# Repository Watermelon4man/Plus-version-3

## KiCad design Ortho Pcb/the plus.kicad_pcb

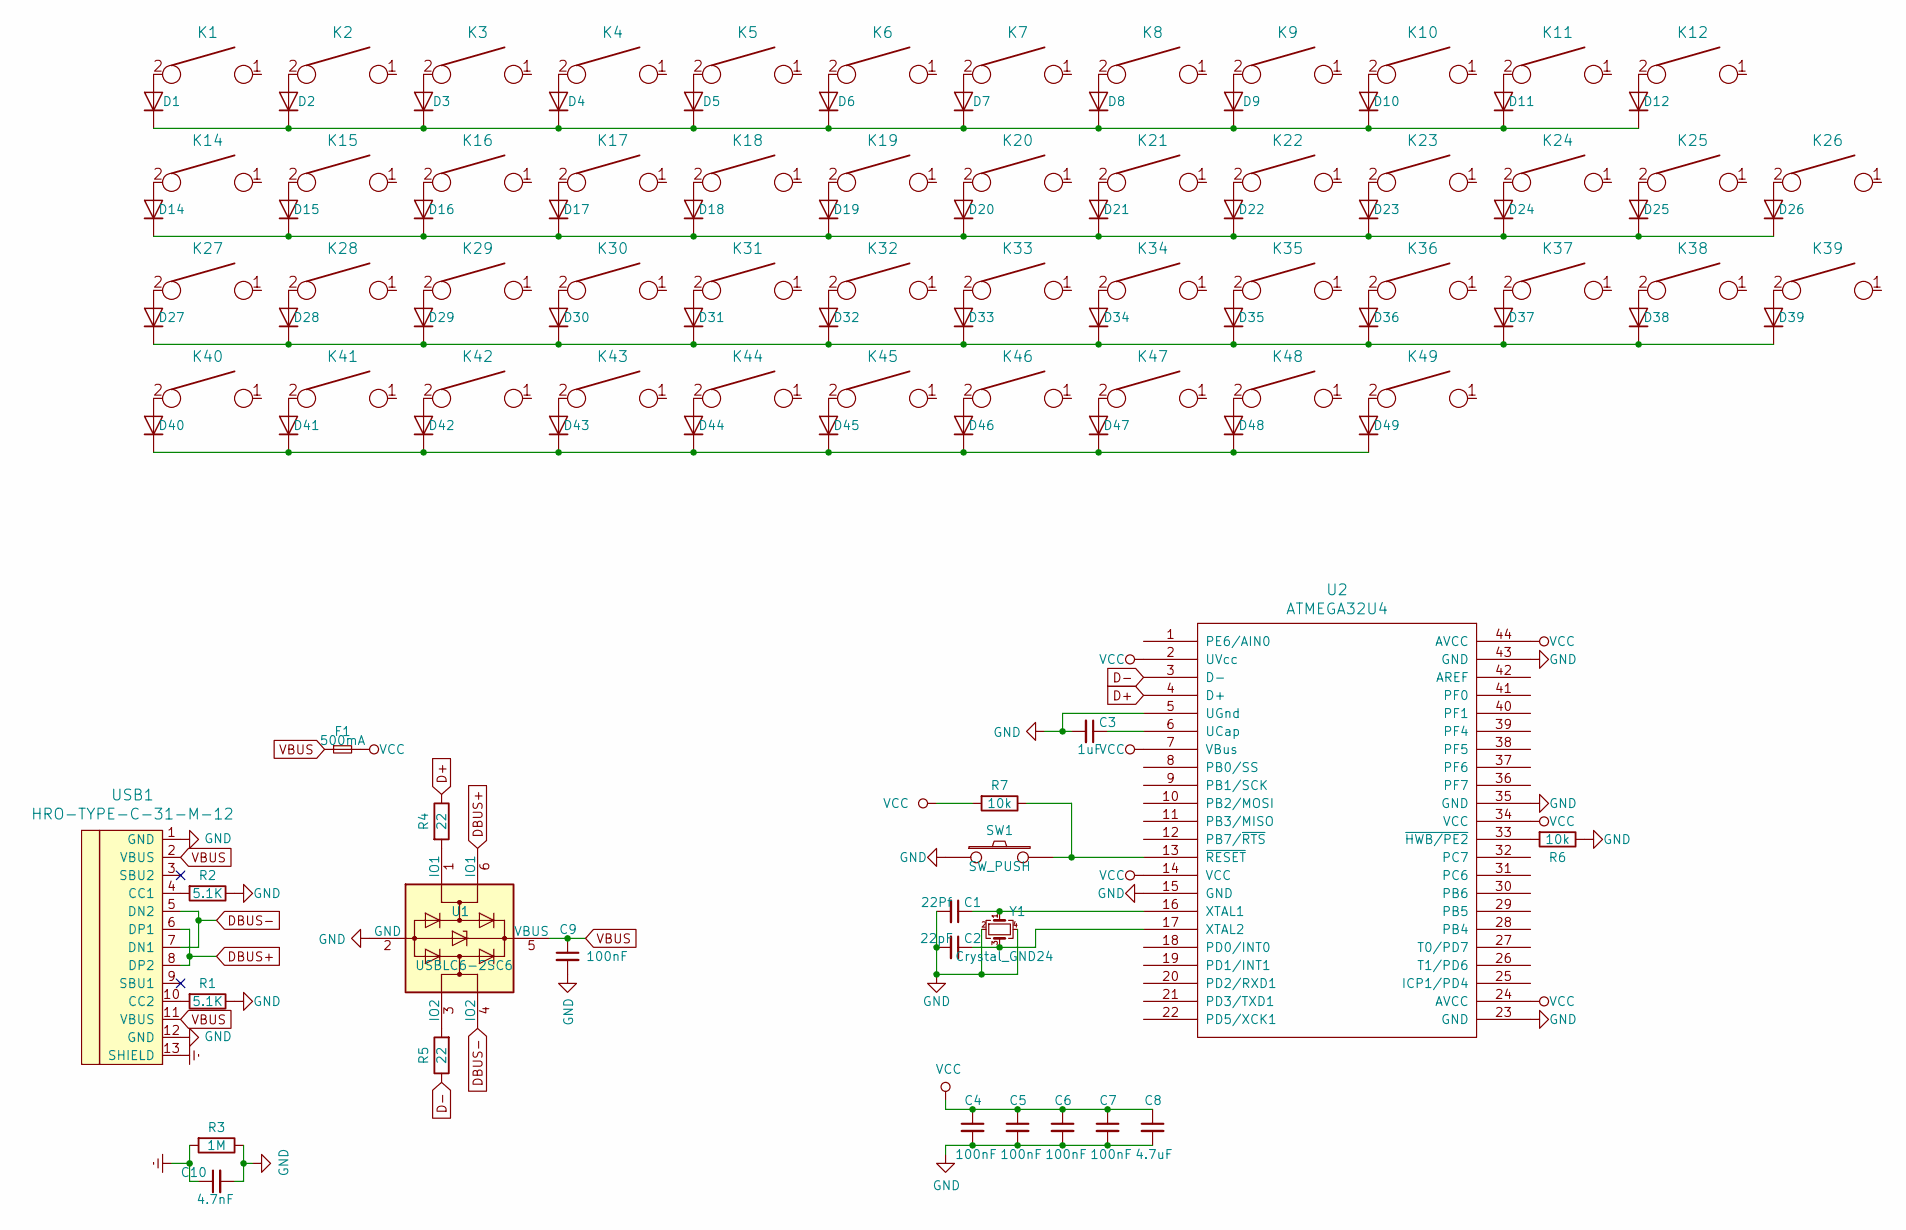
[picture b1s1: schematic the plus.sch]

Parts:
C1: 22Pf; C_0402_1005Metric
C2: 22pF; C_0402_1005Metric
C3: 1uF; C_0402_1005Metric
C4, C5, C6, C7, C9: 100nF; C_0402_1005Metric
C8: 4.7uF; C_0402_1005Metric
C10: 4.7nF; C_0402_1005Metric
D1, D2, D3, D4, D5, D6, D7, D8, D9, D10, D11, D12, D14, D15, D16, D17, D18, D19, D20, D21, D22, D23, D24, D25, D26, D27, D28, D29, D30, D31, D32, D33, D34, D35, D36, D37, D38, D39, D40, D41, D42, D43, D44, D45, D46, D47, D48, D49: 1N4148W; D_SOD-123
F1: 500mA; Fuse_0603_1608Metric
K1, K2, K3, K4, K5, K6, K7, K8, K9, K10, K11, K12, K14, K15, K16, K17, K18, K19, K20, K21, K22, K23, K24, K25, K26, K27, K28, K29, K30, K31, K32, K33, K34, K35, K36, K37, K38, K39, K40, K41, K42, K43, K44, K45, K46, K47, K48, K49: KEYSW; MXOnly-1U-NoLED
R1, R2: 5.1K; R_0402_1005Metric
R3: 1M; R_0402_1005Metric
R4, R5: 22; R_0402_1005Metric
R6, R7: 10k; R_0402_1005Metric
SW1: SW_PUSH; SW_SPST_SKQG_WithoutStem
U1: USBLC6-2SC6; SOT-23-6
U2: ATMEGA32U4; QFP80P1200X1200X120-44N
USB1: HRO-TYPE-C-31-M-12; HRO-TYPE-C-31-M-12-Assembly
Y1: Crystal_GND24; Crystal_SMD_SeikoEpson_FA238-4Pin_3.2x2.5mm

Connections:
D+: R4.1, U2.4 (D+)
D-: R5.1, U2.3 (D-)
DBUS+: U1.6 (IO1), USB1.6 (DP1), USB1.8 (DP2)
DBUS-: U1.4 (IO2), USB1.5 (DN2), USB1.7 (DN1)
Earth: C10.1, R3.2, USB1.13 (SHIELD)
GND: C1.2, C2.2, C3.2, C4.2, C5.2, C6.2, C7.2, C8.2, C9.2, C10.2, R1.1, R2.1, R3.1, R6.1, SW1.1, U1.2 (GND), U2.5 (UGnd), U2.15 (GND), U2.23 (GND), U2.35 (GND), U2.43 (GND), USB1.1 (GND), USB1.12 (GND), Y1.2, Y1.4
unnamed: C1.1, U2.16 (XTAL1), Y1.1
unnamed: C2.1, U2.17 (XTAL2), Y1.3
unnamed: C3.1, U2.6 (UCap)
unnamed: D1.1 (K), D2.1 (K), D3.1 (K), D4.1 (K), D5.1 (K), D6.1 (K), D7.1 (K), D8.1 (K), D9.1 (K), D10.1 (K), D11.1 (K), D12.1 (K)
unnamed: D1.2 (A), K1.2
unnamed: D2.2 (A), K2.2
unnamed: D3.2 (A), K3.2
unnamed: D4.2 (A), K4.2
unnamed: D5.2 (A), K5.2
unnamed: D6.2 (A), K6.2
unnamed: D7.2 (A), K7.2
unnamed: D8.2 (A), K8.2
unnamed: D9.2 (A), K9.2
unnamed: D10.2 (A), K10.2
unnamed: D11.2 (A), K11.2
unnamed: D12.2 (A), K12.2
unnamed: D14.1 (K), D15.1 (K), D16.1 (K), D17.1 (K), D18.1 (K), D19.1 (K), D20.1 (K), D21.1 (K), D22.1 (K), D23.1 (K), D24.1 (K), D25.1 (K), D26.1 (K)
unnamed: D14.2 (A), K14.2
unnamed: D15.2 (A), K15.2
unnamed: D16.2 (A), K16.2
unnamed: D17.2 (A), K17.2
unnamed: D18.2 (A), K18.2
unnamed: D19.2 (A), K19.2
unnamed: D20.2 (A), K20.2
unnamed: D21.2 (A), K21.2
unnamed: D22.2 (A), K22.2
unnamed: D23.2 (A), K23.2
unnamed: D24.2 (A), K24.2
unnamed: D25.2 (A), K25.2
unnamed: D26.2 (A), K26.2
unnamed: D27.1 (K), D28.1 (K), D29.1 (K), D30.1 (K), D31.1 (K), D32.1 (K), D33.1 (K), D34.1 (K), D35.1 (K), D36.1 (K), D37.1 (K), D38.1 (K), D39.1 (K)
unnamed: D27.2 (A), K27.2
unnamed: D28.2 (A), K28.2
unnamed: D29.2 (A), K29.2
unnamed: D30.2 (A), K30.2
unnamed: D31.2 (A), K31.2
unnamed: D32.2 (A), K32.2
unnamed: D33.2 (A), K33.2
unnamed: D34.2 (A), K34.2
unnamed: D35.2 (A), K35.2
unnamed: D36.2 (A), K36.2
unnamed: D37.2 (A), K37.2
unnamed: D38.2 (A), K38.2
unnamed: D39.2 (A), K39.2
unnamed 50: D40.1 (K), D41.1 (K), D42.1 (K), D43.1 (K), D44.1 (K), D45.1 (K), D46.1 (K), D47.1 (K), D48.1 (K), D49.1 (K); also elsewhere on the board
unnamed: D40.2 (A), K40.2
unnamed: D41.2 (A), K41.2
unnamed: D42.2 (A), K42.2
unnamed: D43.2 (A), K43.2
unnamed: D44.2 (A), K44.2
unnamed: D45.2 (A), K45.2
unnamed 57: D46.2 (A), K46.2; also elsewhere on the board
unnamed 58: D47.2 (A), K47.2; also elsewhere on the board
unnamed 59: D48.2 (A), K48.2; also elsewhere on the board
unnamed 60: D49.2 (A), K49.2; also elsewhere on the board
unnamed 67: K7.1; also elsewhere on the board
unnamed 106: K47.1; also elsewhere on the board
unnamed 107: K48.1; also elsewhere on the board
unnamed 108: K49.1; also elsewhere on the board
unnamed: R1.2, USB1.10 (CC2)
unnamed: R2.2, USB1.4 (CC1)
unnamed: R4.2, U1.1 (IO1)
unnamed: R5.2, U1.3 (IO2)
unnamed: R6.2, U2.33 (~HWB/PE2)
unnamed: R7.1, SW1.2, U2.13 (~RESET)
VBUS: C9.1, F1.1, U1.5 (VBUS), USB1.2 (VBUS), USB1.11 (VBUS)
VCC: C4.1, C5.1, C6.1, C7.1, C8.1, F1.2, R7.2, U2.2 (UVcc), U2.7 (VBus), U2.14 (VCC), U2.24 (AVCC), U2.34 (VCC), U2.44 (AVCC)

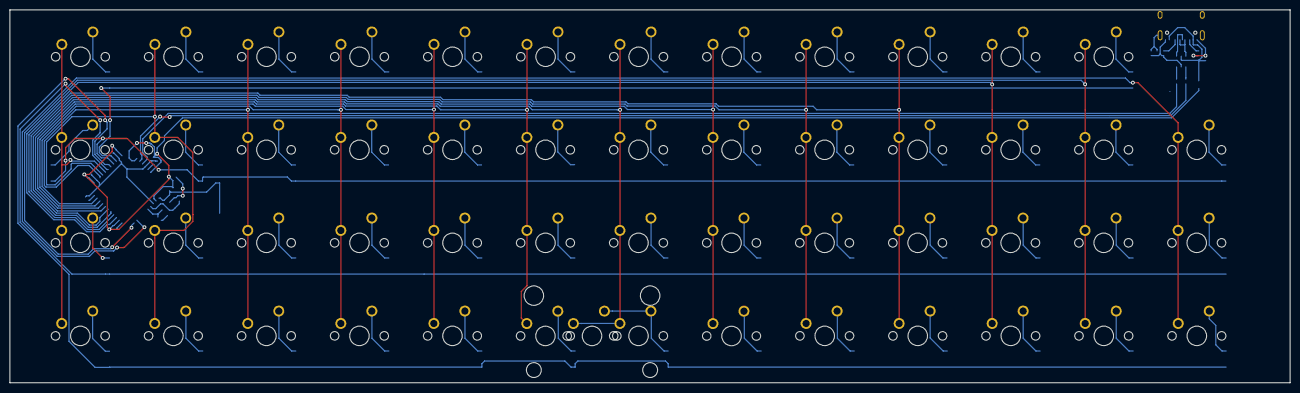
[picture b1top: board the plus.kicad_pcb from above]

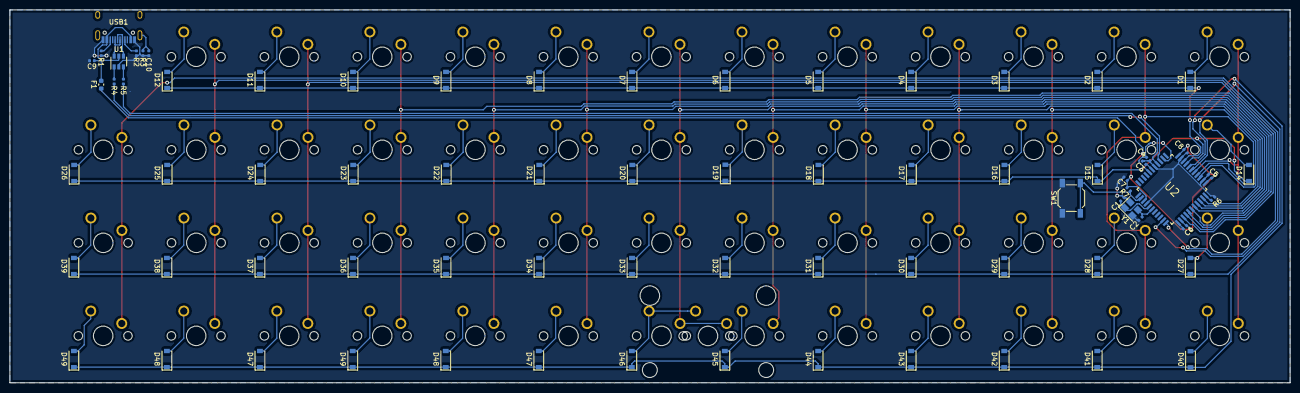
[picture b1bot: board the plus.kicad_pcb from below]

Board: 2 copper layers, 262.1 x 76.3 mm, 126 parts (74 on the bottom side), 73 nets.

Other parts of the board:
D47#2, D48#2, D49#2: 1N4148W; D_SOD-123
K47#2, K48#2, K49#2: KEYSW; MXOnly-1U-NoLED
K53: 2U; MXOnly-2U-ReversedStabilizers-NoLED

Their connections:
unnamed 50: D47#2.1, D48#2.1, D49#2.1; also elsewhere on the board
unnamed 57: K53.2; also elsewhere on the board
unnamed 58: D47#2.2, K47#2.2; also elsewhere on the board
unnamed 59: D48#2.2, K48#2.2; also elsewhere on the board
unnamed 60: D49#2.2, K49#2.2; also elsewhere on the board
unnamed 67: K53.1; also elsewhere on the board
unnamed 106: K47#2.1; also elsewhere on the board
unnamed 107: K48#2.1; also elsewhere on the board
unnamed 108: K49#2.1; also elsewhere on the board
